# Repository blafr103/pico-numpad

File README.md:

# pico-numpad

Custom-built 17-key USB HID numpad powered by a Raspberry Pi Pico W,
featuring a hand-wired switch matrix, 16×2 LCD interface,
host-integrated PC monitoring, weather display, and onboard calculator.

The enclosure, electronics, and firmware were designed specifically for
this project using CircuitPython with event-driven matrix scanning via
`keypad.KeyMatrix`.

This README documents the hand-wired prototype. A custom two-layer PCB
successor built around a bare RP2040 is documented in
[`hardware/`](hardware/).

## Features

- USB HID numeric keypad
- Event-driven matrix scanning (`keypad.KeyMatrix`)
- 16x2 LCD with switchable views:
  - Clock + weather (current conditions and local time for one of
    four preset Canadian locations; date + time synced from the host)
  - PC stats, 4 cycling pages: overview (CPU/GPU utilization,
    temperature, package power), memory (RAM utilization, DIMM
    temperatures, VRAM), clocks (P/E-core max, GPU, TjMax
    distance), and voltages
  - Calculator (+ - * / with standard precedence; expression on
    row 0, result on Enter; keys are captured while active and
    send nothing to the PC)
  - Lifetime keypress statistics
- NumLock doubles as a momentary Fn key:
  - Fn+0: Clock view; pressed again while on it, cycles the
    weather location
  - Fn+1: PC stats view; pressed again while on it, cycles the
    stat pages
  - Fn+2: Calculator view; pressed again while on it, clears
  - Fn+3: Statistics view
  - Fn+'+': Increase keypad LED brightness
  - Fn+'-': Decrease keypad LED brightness
- Persistent settings (lifetime key counter and LED brightness) are stored in the
CircuitPython filesystem (`/count.txt` on internal flash).
- Automatic LCD backlight/LED timeout after 300 seconds of inactivity
- Optional Python companion application providing local time,
weather (Environment Canada API), and PC hardware monitoring.

<p align="center">
  <table align="center">
    <tr>
      <td align="center" width="450" valign="top">
        <br>
        <b>Finished Device</b>
      </td>
      <td align="center" width="470" valign="top">
        <br>
        <b>Hand-Wired Matrix</b>
      </td>
    </tr>
  </table>
</p>

## Physical Construction

This prototype is entirely hand-built rather than assembled on a PCB. The
hand-wired construction allowed the electrical design, firmware, and enclosure
to be developed and validated before committing to a dedicated PCB. That board
now exists as rev A and is documented in [`hardware/`](hardware/).

### Enclosure

- Designed from scratch in Autodesk Fusion 360
- 3D printed on a Bambu Lab X1 Carbon using PETG for the structural components and translucent polycarbonate (PC) for the light-diffusing enclosure 
- Two-piece printed enclosure with integrated LCD mount and switch plate
- Translucent white PC diffuses the per-key LEDs

### Switches & Keycaps

- Switches: Gateron KS-9 G Pro Black linear switches
- Keycaps: Ranked POM Jelly Premium Translucent keycaps

### Key Matrix

The keypad is wired as a 5×4 switch matrix with one diode per key to eliminate
ghosting.

Color coding throughout the wiring:

| Color | Function |
| :--- | :--- |
| **Red** | Matrix columns |
| **Yellow** | Matrix rows |
| **Orange** | LED power distribution |
| **Black** | LED ground |

Each switch includes a **1N4148** diode (anode toward the row, cathode toward
the column), matching the firmware configuration
(`columns_to_anodes=False`). The matrix layout and diode orientation were
verified using the included `tools/matrix_map_test.py` and
`tools/diode_test.py` utilities.

Note that the rev A PCB in [`hardware/`](hardware/) uses the opposite
orientation (cathode to row).

### Lighting

- One discrete white LED beneath each key
- LEDs share a common PWM-controlled supply, with each LED using its own **100 Ω** current-limiting resistor
- Brightness is adjustable in 12.5% increments using **Fn + '+'** and **Fn + '-'**
- The selected brightness is persisted across power cycles
- LEDs turn off together with the LCD backlight after the inactivity timeout and are restored automatically on activity

### Electronics

- Raspberry Pi Pico W mounted internally
- HD44780-compatible 16×2 LCD with PCF8574 I²C backpack

## Hardware

- Raspberry Pi Pico W (RP2040), CircuitPython 9.2.1
- 16×2 HD44780-compatible LCD with PCF8574 I²C backpack (0x27)
- 17 Gateron KS-9 G Pro Black switches
- Ranked POM Jelly translucent keycaps
- 17 white discrete LEDs
- Rows: GP2–GP6
- Columns: GP12–GP15
- Key LEDs (PWM): GP11
- I²C: SDA GP0 · SCL GP1

## Install

1. Flash CircuitPython 9.x to the Pico.
2. Copy `code.py`, `boot.py`, and `lib/` to the CIRCUITPY drive,
   then power cycle (`boot.py` changes only apply at power-up).
   - On first boot, the firmware creates `/count.txt` to store persistent settings (currently the lifetime keypress count and LED brightness).
3. Install `adafruit_hid` from the
   [CircuitPython 9.x library bundle](https://circuitpython.org/libraries)
   into `lib/`.
4. Optional, for the clock, weather, and PC stats:
   `pip install pyserial requests env_canada` on the PC and run
   `python host/companion.py`. The pad is fully functional without
   it; the clock shows UNKNOWN, weather shows "no weather", and PC
   stats show "no data" until first contact.
   - The Pico exposes two serial ports; the script auto-detects
     the data port, or set PORT in the script manually.
   - PC stats additionally require
     [LibreHardwareMonitor](https://github.com/LibreHardwareMonitor/LibreHardwareMonitor)
     running as administrator with its web server enabled
     (Options - Remote Web Server - Run). Time and weather work
     without it.
   - Weather locations are configured in companion.py as
     label + coordinates + IANA timezone.
   - For hands-off startup on Windows (Task Scheduler setup, logging,
    troubleshooting), see [host/README.md](host/README.md).

## Design

Matrix scanning and debouncing run in C in the background
(`keypad.KeyMatrix`, 10 ms interval); the main loop only consumes
queued edge events, so a busy loop delays input rather than dropping
it. HID output uses `press()`/`release()` on edges so the host sees
real held keys and handles auto-repeat. A hand-written equivalent of
the scanner (polling, per-key debounce state machine) is kept in
[`reference/`](reference/) with a comparison of the two approaches.

`columns_to_anodes=False` is required for this board's diode
orientation; the default silently reads all keys as dead.

`boot.py` remounts the filesystem to allow the firmware to save the
persistent key counter. Holding **NumLock** while connecting the Pico
starts a development mode that leaves the drive writable from the host
and disables persistence.

The LCD is driven with no `sleep()` in the main loop: dirty-flag
rendering (I²C writes only on state change), fixed-width line
overwrites instead of `clear()`, and edge-triggered backlight
control. A full LCD line write costs ~50 ms over I²C, so
unconditional redraws would starve input latency.

The LCD is organized as switchable views (splash on boot, clock,
PC stats, calculator, statistics). Holding **NumLock** acts as a
momentary Fn key: tapping a digit while held switches views without
typing it. A plain NumLock tap is deferred until release so tap and
hold can be distinguished without affecting normal typing. Each view
owns its input: most pass keys through to the PC as normal typing,
while the calculator captures digits and operators entirely
(including suppressing their release events), so nothing leaks to
the host while it is active.

The calculator stores the expression as typed (row 0, scrolling
left past 16 characters) and evaluates on Enter with standard
precedence: tokens are reduced in two passes, folding `*` and `/`
left-to-right first, then summing the remaining `+`/`-` terms.
Divide-by-zero shows Error, cleared by the next digit. After a
result, a digit starts a fresh expression and an operator continues
from the result. Results too wide for the row use scientific
notation. Leaving the view clears it.

Time, weather, and PC stats come from an optional host script
(`host/companion.py`, setup and operation in
[host/README.md](host/README.md)) over a second USB CDC serial port
enabled in `boot.py`. The protocol is newline-terminated ASCII `key:value` lines;
the Pico is a pure listener and the host broadcasts unsolicited (time
on connect and every 30 s, stats every 2 s, weather every 10 min).
The clock free-runs on the crystal between syncs and re-anchors on
every message, bounding drift to one broadcast interval. The RP2040
has no battery-backed RTC, so time is lost at power-off and shows
UNKNOWN until the first sync.

Weather comes from Environment Canada via the `env_canada` package
(nearest site to each configured coordinate). The clock view shows
one location's conditions on row 0 and its local date/time on row 1;
the host sends each location's UTC-offset delta computed fresh with
`zoneinfo`, so DST is handled entirely host-side. Weather older than
30 minutes displays as stale (`LABEL --`); PC stats older than 15
seconds display as "no data".

PC stat rows are composed entirely on the host: companion.py reads
LibreHardwareMonitor's JSON endpoint, selects sensors by hardware
prefix and display name (numeric sensor indices shift between LHM
versions), and sends each page row as a finished 16-character line.
The Pico renders these verbatim, apart from substituting `*` with
the LCD's degree symbol, so adding or reworking a stat page is a
host-only change. Missing sensors render as `--`; the sensor names
target this machine's hardware and need adjusting for others.

Persistent settings (currently the lifetime keypress count and LED brightness) 
are stored in `/count.txt`. To minimize flash wear, writes are batched 
(100 keypresses by default) and also occur immediately after brightness 
changes and when the device transitions to the idle state.

The firmware is organized into independent subsystems for input handling,
LCD rendering, view management, HID output, persistent settings, and host 
communication.

## Future Improvements

- User-configurable key mapping and macros
- More robust persistent configuration storage
  
The custom PCB, integrated USB-C, and per-key RGB lighting items previously
listed here are addressed by the rev A board in [`hardware/`](hardware/).

## Tools

- `tools/matrix_map_test.py` prints (row, col) per keypress; used
  to build/verify the keymap
- `tools/diode_test.py` is a bidirectional scan; verifies diode
  presence and orientation per key

Run either by copying to CIRCUITPY as `code.py` (back up first) and
watching the serial console. Run in dev mode (NumLock at plug-in)
so the drive is writable.

## Credits

LCD driver (`lib/lcd.py`, `lib/i2c_pcf8574_interface.py`):
[dwhall/circuitpython_lcd](https://github.com/dwhall/circuitpython_lcd),
original license headers retained.

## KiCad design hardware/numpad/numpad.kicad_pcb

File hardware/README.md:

# pico-numpad - Hardware

Custom two-layer PCB for a 17-key USB numpad with per-key RGB, a rotary encoder, and a 16x2 character LCD. This is the custom-board successor to the hand-wired CircuitPython numpad documented in the repository root, rebuilt around a bare RP2040 with hot-swap switches.
 
**Status - Rev A.** Design complete, DRC clean, full design review passed. Boards fabricated by PCBWay (ENIG) and hand-assembled. Electrical bring-up is **in progress and incomplete** - the board does not yet enumerate over USB and the 3.3 V rail is under investigation. The C firmware targeting this board has been started but is not yet functional. Treat the design as unvalidated.
 
Designed in KiCad 10.

---

## Features

- Bare **RP2040** (not a Pico module) with 16 MB **W25Q128** QSPI flash and a 12 MHz crystal
- **17 hot-swap keys** on Kailh MX sockets (CPG151101S11), any MX-style switch
- **Per-key RGB** - 17x SK6812MINI-E, 5 V data driven through a 74AHCT1G125 level buffer
- **Rotary encoder** with push (EC11), push mapped into the key matrix
- **16x2 HD44780 LCD** over I2C (PCF8574 backpack), driven through an onboard level shifter and connected via header
- **USB-C** with dual 5.1 kΩ CC pulldowns, USBLC6-2SC6 ESD protection, and 27 Ω series termination
- 5x4 diode-per-key matrix, one 1N4148 per switch, **cathode to row** (COL2ROW). This is the reverse of the hand-wired build, which is wired anode to row.
- BOOTSEL and RESET buttons, SWD header
- Screws enter from either face (bottom edge extended so the lower mounting holes clear the 0 and Enter keycaps)

---

## Repository layout

```
hardware/
├── README.md                            this file
├── numpad/
│   ├── numpad.kicad_pro                 KiCad project
│   ├── numpad.kicad_prl                 project-local settings (editor state, netclasses)
│   ├── numpad.kicad_pcb                 board
│   ├── numpad.kicad_sch                 schematic, root sheet
│   ├── 01_power_usb.kicad_sch           USB-C, ESD, 3.3 V regulator
│   ├── 02_mcu.kicad_sch                 RP2040, QSPI flash, crystal, SWD, BOOTSEL/RESET
│   ├── 03_matrix.kicad_sch              key matrix and rotary encoder
│   ├── 04_rgb.kicad_sch                 SK6812 chain and 74AHCT1G125 buffer
│   ├── 05_ui.kicad_sch                  LCD header and I2C level shifters
│   ├── fp-lib-table                     footprint library table
│   ├── sym-lib-table                    symbol library table
│   ├── numpad.csv                       BOM export from the schematic
│   ├── part-numbers.txt                 working notes on ordered part numbers
│   ├── lib/marbastlib/                  git submodule - MX symbols/footprints, Kailh sockets
│   ├── plot-files/                      raw KiCad plot output - all gerbers, both drill maps, DXF, drills
│   ├── numpad-revA-fab/                 cleaned fab set actually sent to the fab (12 files)
│   ├── numpad-revA-fab.zip              the same set, zipped for upload
│   ├── step-files/                      board STEP for the enclosure model
│   └── W1129510AS1K1.pdf                PCBWay order document, W1129510AS1K1
├── stencil_gerbers/                     paste and outline set sent for the SMD stencils
├── stencil_gerbers.zip                  the same set, zipped for upload
├── production file W1129510AS1K2/       PCBWay's returned CAM data for W1129510AS1K2
└── production file W1129510AS1K2.zip    the same, as delivered
```

`numpad/lib/marbastlib` is a submodule. After cloning:

```
git submodule update --init --recursive
```

---

## Board summary

| | |
|---|---|
| Size | 83 x 127 mm |
| Layers | 2 |
| Thickness | 1.6 mm |
| Copper | 1 oz |
| Min track / clearance | 0.2 mm / 0.15 mm |
| Vias | 0.6 / 0.3 mm |
| Footprints | 120 |

Switches and RGB are surface-mount on the **back** copper (marbastlib MX footprints are authored for back-side placement). The USB/MCU/encoder strip sits along the top edge on the front.

---

## Key matrix

17 keys plus the encoder push occupy 18 of the 20 cells in a 5x4 grid. The 2u-tall `+` and `Enter` keys each take a single electrical cell, at R1C3 and R4C3, which leaves R2C3 free for the encoder push and R3C3 unused. The 2u-wide `0` key leaves R4C1 unused.

| | C0 | C1 | C2 | C3 |
|----|-----|---------|-----|--------------|
| R0 | Num | /       | *   | -            |
| R1 | 7   | 8       | 9   | +            |
| R2 | 4   | 5       | 6   | Encoder push |
| R3 | 1   | 2       | 3   | (unused)     |
| R4 | 0   | (unused) | .  | Enter        |

---

## Notable ICs and interfaces

| Ref | Part | Role |
|-----|------|------|
| U3  | RP2040 | MCU, QFN-56, 0.4 mm pitch |
| U4  | W25Q128JVS | 16 MB QSPI program flash |
| U1  | NCP1117-3.3 | 3.3 V LDO (see substitution note below) |
| U2  | USBLC6-2SC6 | USB ESD protection |
| U5  | 74AHCT1G125 | 3.3 V to 5 V buffer for the RGB data line |
| Q1/Q2 | BSS138 x2 | I2C level shift for the LCD header |
| J1  | USB-C receptacle (HRO TYPE-C-31-M-12) | Power and data |
| J2  | SWD header | Debug |
| J3  | LCD header | I2C to the character LCD |

Exact GPIO assignments live in the schematic and are the source of truth for firmware. Verified against the KiCad netlist: RGB data on **GP11**, encoder A/B on **GP7/GP8**. The matrix rows (GP2-GP6), columns (GP12-GP15), and I2C (GP0/GP1) carry over unchanged from the hand-wired build. GP11 changes role, it drove the single-colour LED PWM on the hand-wired unit and drives the SK6812 chain here. The encoder is new to this board.

---

## Ordering this board

Fab specs, all inside a standard 2-layer capability:
 
- 2-layer, 1.6 mm FR-4, 1 oz copper
- 6/6 mil track/space class, 0.3 mm minimum drill
- **ENIG recommended.** The RP2040 is a 0.4 mm-pitch QFN-56 - a flat immersion-gold finish wets far more predictably under hand soldering than domed HASL
- 
The board has **6 intentional plated slots** (4 at the USB-C connector shield legs, 2 at the encoder bracket), written as route-mode Excellon (`G00/M15/M16`) rather than G85. Most CAM tools read this correctly, but it is worth confirming in the fab's gerber viewer that they render as elongated openings.

---

## Assembly and bring-up

The board is designed for **staged bring-up**, not a single reflow:
 
1. Populate the USB-C and regulator section first. Scope the 3.3 V rail under a ~100 Ω load (AC-coupled, bandwidth-limited, short ground spring) and confirm it is not oscillating **before** placing the RP2040.
2. Then place the MCU, flash, and crystal, and confirm enumeration over USB.
3. Then the switch matrix, encoder, RGB chain, and LCD header.

Two part choices worth considering before assembly:
 
- **Regulator.** The board is drawn for the NCP1117ST33T3G, but C2 is a 10 µF MLCC that sits below that regulator's 0.25-2.2 Ω output-ESR floor. If the 3.3 V rail oscillates, swap in a ceramic-stable **TLV1117-33** (same SOT-223 pinout, drop-in). Recommend ordering both for cheap insurance.
- **Crystal.** 12 MHz 3225, chosen for **CL ≈ 18 pF** to match the 27 pF loading caps. Check the specific part's max ESR - higher-CL parts trend higher ESR, and higher CL also slows startup, which may need the pico-sdk XOSC startup multiplier raised. A CL = 10 pF part with 15 pF caps is a BOM-only fallback if either becomes a problem.

---

## Firmware

The hand-wired numpad in the repository root runs **CircuitPython** on a Pico W. That firmware does **not** port directly to this board - the bare RP2040 boot flow, the encoder, and RGB (vs single-color PWM) all differ, as does the diode orientation. The matrix and I2C pin assignments do carry over.
 
The custom board is designed to run a **C firmware on pico-sdk + TinyUSB**. That rewrite has been started and is not yet functional.

---

## License

The files in this repository are covered by the license terms in the repository root.
 
The KiCad symbols and footprints under `numpad/lib/marbastlib` are a git submodule of [ebastler/marbastlib](https://github.com/ebastler/marbastlib), licensed **CERN-OHL-P-2.0**. Those terms, including its notice requirements, apply to that library and to the footprints used from it.

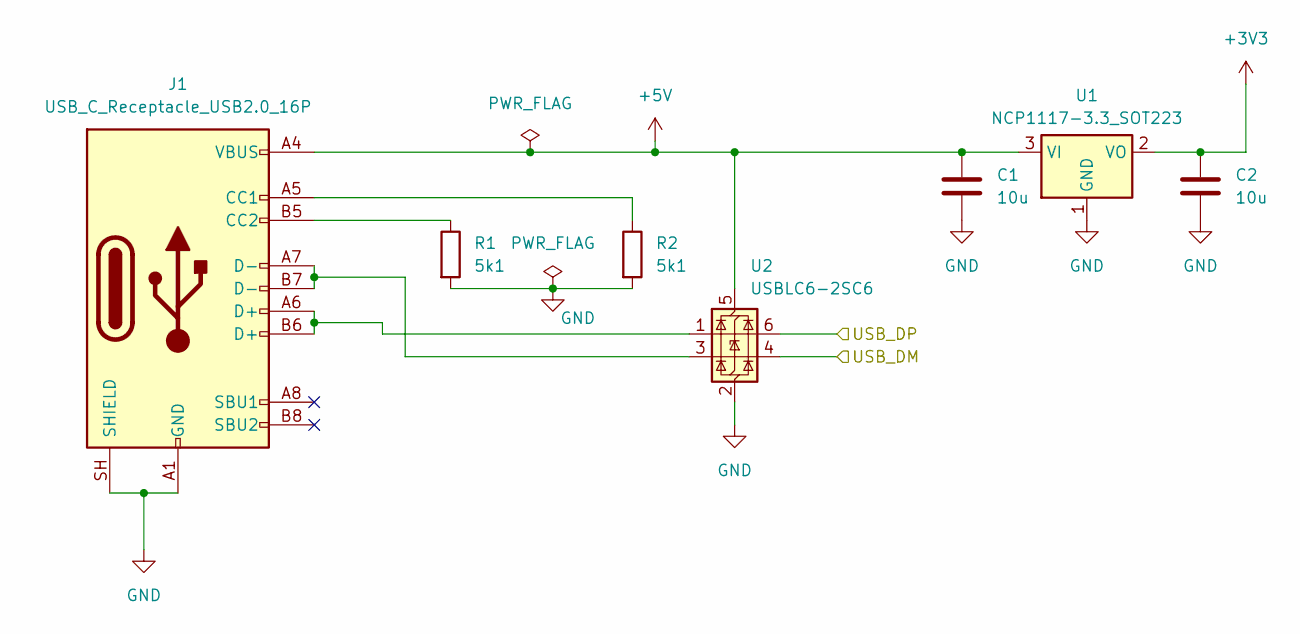
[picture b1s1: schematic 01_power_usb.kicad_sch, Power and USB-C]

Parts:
C1, C2: 10u; C_0805_2012Metric
J1: USB_C_Receptacle_USB2.0_16P; USB_C_Receptacle_HRO_TYPE-C-31-M-12
R1, R2: 5k1; R_0603_1608Metric
U1: NCP1117-3.3_SOT223; SOT-223-3_TabPin2
U2: USBLC6-2SC6; SOT-23-6

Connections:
+3V3: C2.1, U1.2 (VO); also elsewhere on the board
+5V: C1.1, J1.A4 (VBUS), J1.A9 (VBUS), J1.B4 (VBUS), J1.B9 (VBUS), U1.3 (VI), U2.5 (VBUS); also elsewhere on the board
/01_power_usb/USB_DM: U2.4 (I/O2); also elsewhere on the board
/01_power_usb/USB_DP: U2.6 (I/O1); also elsewhere on the board
GND: C1.2, C2.2, J1.A1 (GND), J1.A12 (GND), J1.B1 (GND), J1.B12 (GND), J1.SH (SHIELD), R1.2, R2.2, U1.1 (GND), U2.2 (GND); also elsewhere on the board
unnamed: J1.A5 (CC1), R2.1
unnamed: J1.B5 (CC2), R1.1
unnamed: J1.A6 (D+), J1.B6 (D+), U2.1 (I/O1)
unnamed: J1.A7 (D-), J1.B7 (D-), U2.3 (I/O2)

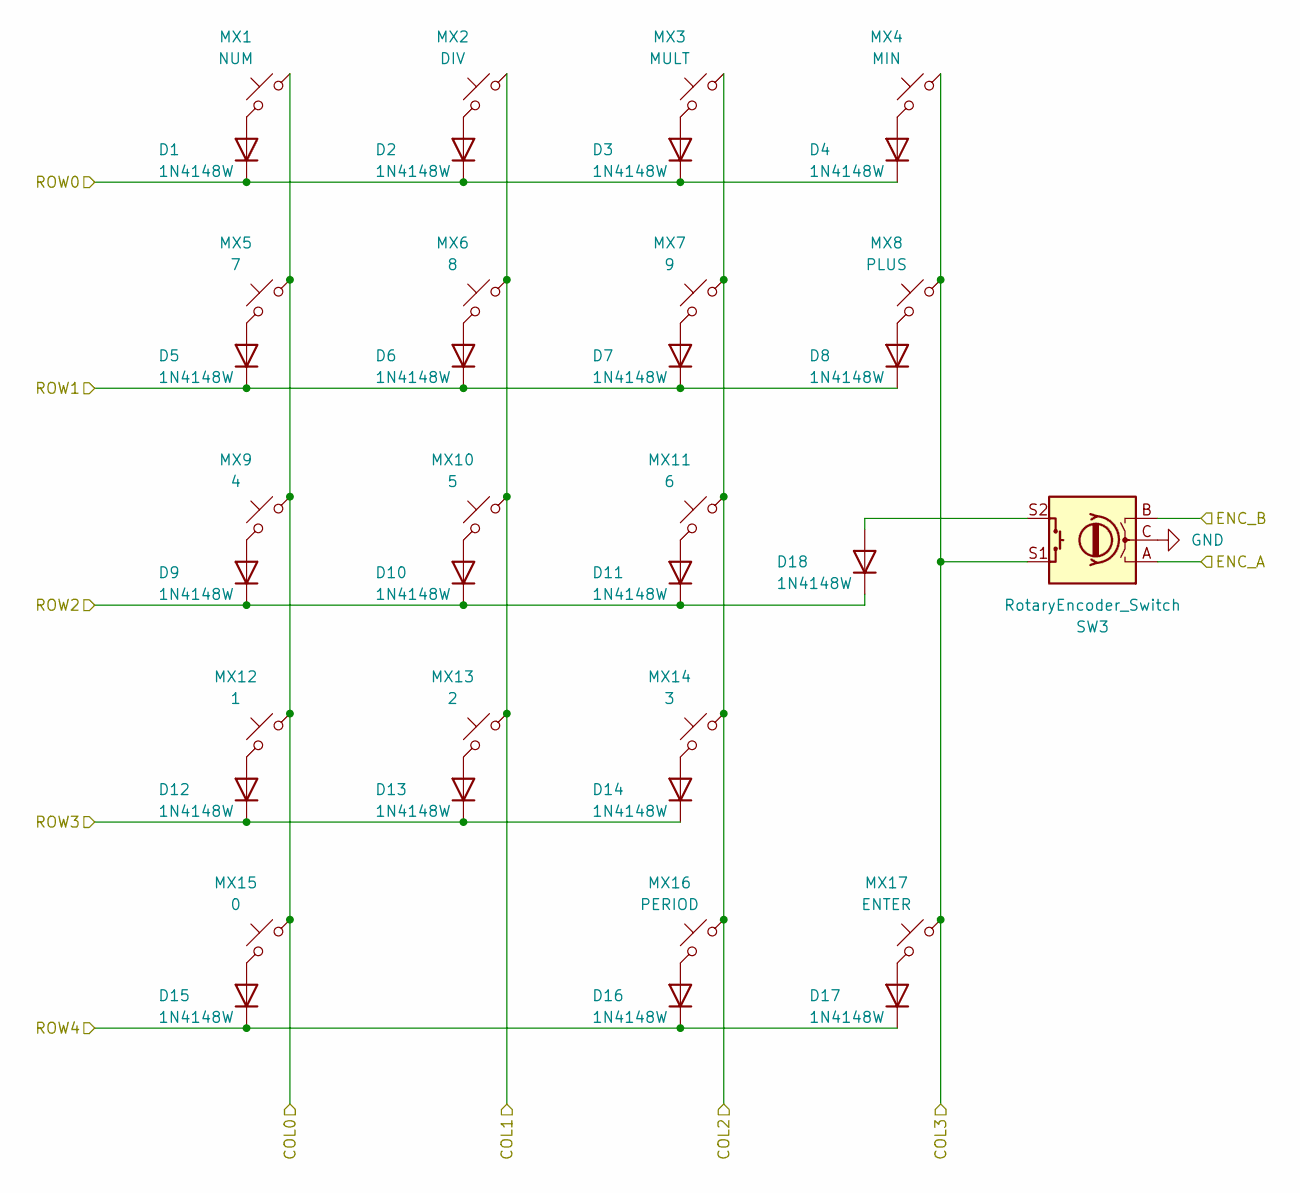
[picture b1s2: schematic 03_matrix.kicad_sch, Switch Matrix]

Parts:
D1, D2, D3, D4, D5, D6, D7, D8, D9, D10, D11, D12, D13, D14, D15, D16, D17, D18: 1N4148W; D_SOD-123
MX1: NUM; SW_MX_HS_CPG151101S11_1u
MX2: DIV; SW_MX_HS_CPG151101S11_1u
MX3: MULT; SW_MX_HS_CPG151101S11_1u
MX4: MIN; SW_MX_HS_CPG151101S11_1u
MX5: 7; SW_MX_HS_CPG151101S11_1u
MX6: 8; SW_MX_HS_CPG151101S11_1u
MX7: 9; SW_MX_HS_CPG151101S11_1u
MX8: PLUS; SW_MX_HS_CPG151101S11_1u
MX9: 4; SW_MX_HS_CPG151101S11_1u
MX10: 5; SW_MX_HS_CPG151101S11_1u
MX11: 6; SW_MX_HS_CPG151101S11_1u
MX12: 1; SW_MX_HS_CPG151101S11_1u
MX13: 2; SW_MX_HS_CPG151101S11_1u
MX14: 3; SW_MX_HS_CPG151101S11_1u
MX15: 0; SW_MX_HS_CPG151101S11_1u
MX16: PERIOD; SW_MX_HS_CPG151101S11_1u
MX17: ENTER; SW_MX_HS_CPG151101S11_1u
SW3: RotaryEncoder_Switch; RotaryEncoder_Alps_EC11E-Switch_Vertical_H20mm

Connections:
/02_mcu/COL0: MX1.2, MX5.2, MX9.2, MX12.2, MX15.2; also elsewhere on the board
/02_mcu/COL1: MX2.2, MX6.2, MX10.2, MX13.2; also elsewhere on the board
/02_mcu/COL2: MX3.2, MX7.2, MX11.2, MX14.2, MX16.2; also elsewhere on the board
/02_mcu/COL3: MX4.2, MX8.2, MX17.2, SW3.S1; also elsewhere on the board
/02_mcu/ENC_A: SW3.A; also elsewhere on the board
/02_mcu/ENC_B: SW3.B; also elsewhere on the board
/02_mcu/ROW0: D1.1 (K), D2.1 (K), D3.1 (K), D4.1 (K); also elsewhere on the board
/02_mcu/ROW1: D5.1 (K), D6.1 (K), D7.1 (K), D8.1 (K); also elsewhere on the board
/02_mcu/ROW2: D9.1 (K), D10.1 (K), D11.1 (K), D18.1 (K); also elsewhere on the board
/02_mcu/ROW3: D12.1 (K), D13.1 (K), D14.1 (K); also elsewhere on the board
/02_mcu/ROW4: D15.1 (K), D16.1 (K), D17.1 (K); also elsewhere on the board
GND: SW3.C; also elsewhere on the board
unnamed: D1.2 (A), MX1.1
unnamed: D2.2 (A), MX2.1
unnamed: D3.2 (A), MX3.1
unnamed: D4.2 (A), MX4.1
unnamed: D5.2 (A), MX5.1
unnamed: D6.2 (A), MX6.1
unnamed: D7.2 (A), MX7.1
unnamed: D8.2 (A), MX8.1
unnamed: D9.2 (A), MX9.1
unnamed: D10.2 (A), MX10.1
unnamed: D11.2 (A), MX11.1
unnamed: D12.2 (A), MX12.1
unnamed: D13.2 (A), MX13.1
unnamed: D14.2 (A), MX14.1
unnamed: D15.2 (A), MX15.1
unnamed: D16.2 (A), MX16.1
unnamed: D17.2 (A), MX17.1
unnamed: D18.2 (A), SW3.S2

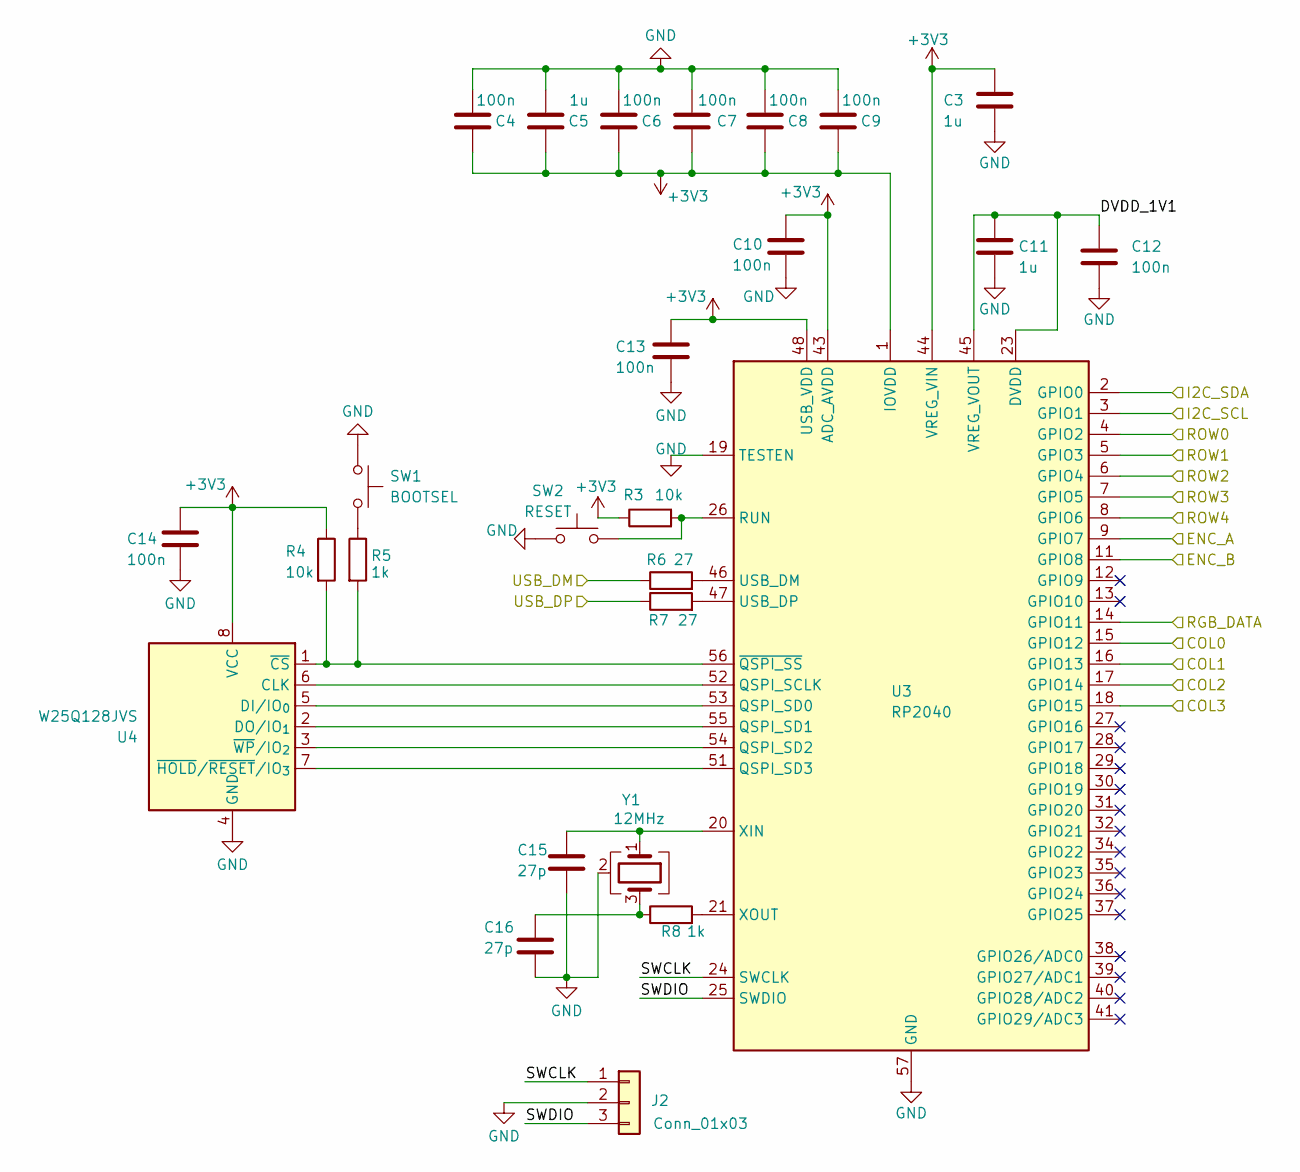
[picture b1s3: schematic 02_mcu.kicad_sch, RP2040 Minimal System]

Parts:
C3, C5, C11: 1u; C_0603_1608Metric
C4, C6, C7, C8, C9, C10, C12, C13, C14: 100n; C_0603_1608Metric
C15, C16: 27p; C_0603_1608Metric
J2: Conn_01x03; PinHeader_1x03_P2.54mm_Vertical
R3, R4: 10k; R_0603_1608Metric
R5, R8: 1k; R_0603_1608Metric
R6, R7: 27; R_0603_1608Metric
SW1: BOOTSEL; SW_SPST_PTS645Sx43SMTR92
SW2: RESET; SW_SPST_PTS645Sx43SMTR92
U3: RP2040; QFN-56-1EP_7x7mm_P0.4mm_EP3.2x3.2mm
U4: W25Q128JVS; SOIC-8_5.3x5.3mm_P1.27mm
Y1: 12MHz; Crystal_SMD_3225-4Pin_3.2x2.5mm

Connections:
+3V3: C3.1, C4.1, C5.1, C6.1, C7.1, C8.1, C9.1, C10.1, C13.1, C14.1, R3.1, R4.1, U3.1 (IOVDD), U3.10 (IOVDD), U3.22 (IOVDD), U3.33 (IOVDD), U3.42 (IOVDD), U3.43 (ADC_AVDD), U3.44 (VREG_VIN), U3.48 (USB_VDD), U3.49 (IOVDD), U4.8 (VCC); also elsewhere on the board
/01_power_usb/USB_DM: R6.1; also elsewhere on the board
/01_power_usb/USB_DP: R7.1; also elsewhere on the board
/02_mcu/COL0: U3.15 (GPIO12); also elsewhere on the board
/02_mcu/COL1: U3.16 (GPIO13); also elsewhere on the board
/02_mcu/COL2: U3.17 (GPIO14); also elsewhere on the board
/02_mcu/COL3: U3.18 (GPIO15); also elsewhere on the board
/02_mcu/DVDD_1V1: C11.1, C12.1, U3.23 (DVDD), U3.45 (VREG_VOUT), U3.50 (DVDD)
/02_mcu/ENC_A: U3.9 (GPIO7); also elsewhere on the board
/02_mcu/ENC_B: U3.11 (GPIO8); also elsewhere on the board
/02_mcu/I2C_SCL: U3.3 (GPIO1); also elsewhere on the board
/02_mcu/I2C_SDA: U3.2 (GPIO0); also elsewhere on the board
/02_mcu/RGB_DATA: U3.14 (GPIO11); also elsewhere on the board
/02_mcu/ROW0: U3.4 (GPIO2); also elsewhere on the board
/02_mcu/ROW1: U3.5 (GPIO3); also elsewhere on the board
/02_mcu/ROW2: U3.6 (GPIO4); also elsewhere on the board
/02_mcu/ROW3: U3.7 (GPIO5); also elsewhere on the board
/02_mcu/ROW4: U3.8 (GPIO6); also elsewhere on the board
/02_mcu/SWCLK: J2.1, U3.24 (SWCLK)
/02_mcu/SWDIO: J2.3, U3.25 (SWDIO)
GND: C3.2, C4.2, C5.2, C6.2, C7.2, C8.2, C9.2, C10.2, C11.2, C12.2, C13.2, C14.2, C15.2, C16.2, J2.2, SW1.1, SW2.1, U3.19 (TESTEN), U3.57 (GND), U4.4 (GND), Y1.2 (G), Y1.4 (G); also elsewhere on the board
unnamed: C16.1, R8.1, Y1.3
unnamed: R5.1, SW1.2
unnamed: U3.52 (QSPI_SCLK), U4.6 (CLK)
unnamed: U3.53 (QSPI_SD0), U4.5 (DI/IO_{0})
unnamed: U3.55 (QSPI_SD1), U4.2 (DO/IO_{1})
unnamed: U3.54 (QSPI_SD2), U4.3 (~WP/IO_{2})
unnamed: U3.51 (QSPI_SD3), U4.7 (~HOLD/~RESET/IO_{3})
unnamed: R3.2, SW2.2, U3.26 (RUN)
unnamed: R6.2, U3.46 (USB_DM)
unnamed: R7.2, U3.47 (USB_DP)
unnamed: C15.1, U3.20 (XIN), Y1.1
unnamed: R8.2, U3.21 (XOUT)
unnamed: R4.2, R5.2, U3.56 (~QSPI_SS), U4.1 (~CS)

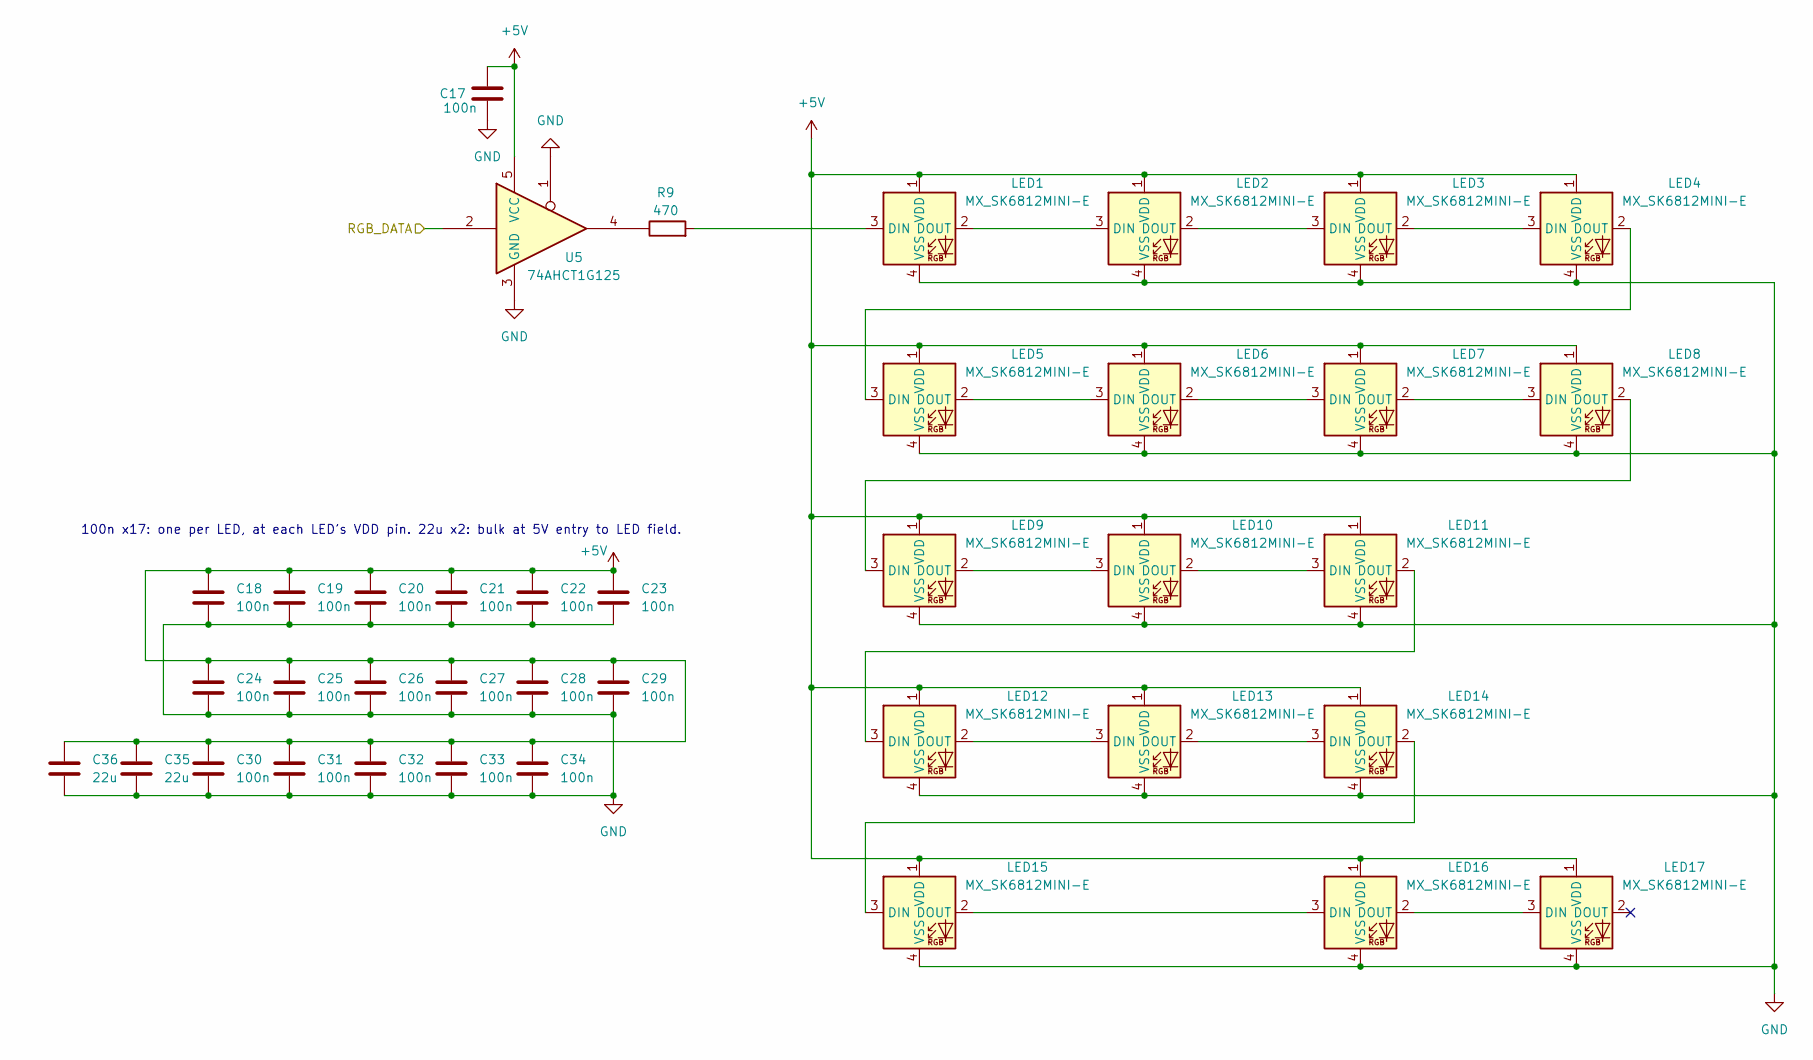
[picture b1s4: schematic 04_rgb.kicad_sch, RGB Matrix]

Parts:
C17, C18, C19, C20, C21, C22, C23, C24, C25, C26, C27, C28, C29, C30, C31, C32, C33, C34: 100n; C_0603_1608Metric
C35, C36: 22u; C_0805_2012Metric
LED1, LED2, LED3, LED4, LED5, LED6, LED7, LED8, LED9, LED10, LED11, LED12, LED13, LED14, LED15, LED16, LED17: MX_SK6812MINI-E; LED_MX_6028R
R9: 470; R_0603_1608Metric
U5: 74AHCT1G125; SOT-23-5

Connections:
+5V: C17.1, C18.1, C19.1, C20.1, C21.1, C22.1, C23.1, C24.1, C25.1, C26.1, C27.1, C28.1, C29.1, C30.1, C31.1, C32.1, C33.1, C34.1, C35.1, C36.1, LED1.1 (VDD), LED2.1 (VDD), LED3.1 (VDD), LED4.1 (VDD), LED5.1 (VDD), LED6.1 (VDD), LED7.1 (VDD), LED8.1 (VDD), LED9.1 (VDD), LED10.1 (VDD), LED11.1 (VDD), LED12.1 (VDD), LED13.1 (VDD), LED14.1 (VDD), LED15.1 (VDD), LED16.1 (VDD), LED17.1 (VDD), U5.5 (VCC); also elsewhere on the board
/02_mcu/RGB_DATA: U5.2; also elsewhere on the board
GND: C17.2, C18.2, C19.2, C20.2, C21.2, C22.2, C23.2, C24.2, C25.2, C26.2, C27.2, C28.2, C29.2, C30.2, C31.2, C32.2, C33.2, C34.2, C35.2, C36.2, LED1.4 (VSS), LED2.4 (VSS), LED3.4 (VSS), LED4.4 (VSS), LED5.4 (VSS), LED6.4 (VSS), LED7.4 (VSS), LED8.4 (VSS), LED9.4 (VSS), LED10.4 (VSS), LED11.4 (VSS), LED12.4 (VSS), LED13.4 (VSS), LED14.4 (VSS), LED15.4 (VSS), LED16.4 (VSS), LED17.4 (VSS), U5.1, U5.3 (GND); also elsewhere on the board
unnamed: LED1.3 (DIN), R9.2
unnamed: LED1.2 (DOUT), LED2.3 (DIN)
unnamed: LED2.2 (DOUT), LED3.3 (DIN)
unnamed: LED3.2 (DOUT), LED4.3 (DIN)
unnamed: LED4.2 (DOUT), LED5.3 (DIN)
unnamed: LED5.2 (DOUT), LED6.3 (DIN)
unnamed: LED6.2 (DOUT), LED7.3 (DIN)
unnamed: LED7.2 (DOUT), LED8.3 (DIN)
unnamed: LED8.2 (DOUT), LED9.3 (DIN)
unnamed: LED9.2 (DOUT), LED10.3 (DIN)
unnamed: LED10.2 (DOUT), LED11.3 (DIN)
unnamed: LED11.2 (DOUT), LED12.3 (DIN)
unnamed: LED12.2 (DOUT), LED13.3 (DIN)
unnamed: LED13.2 (DOUT), LED14.3 (DIN)
unnamed: LED14.2 (DOUT), LED15.3 (DIN)
unnamed: LED15.2 (DOUT), LED16.3 (DIN)
unnamed: LED16.2 (DOUT), LED17.3 (DIN)
unnamed: R9.1, U5.4

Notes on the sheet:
100n x17: one per LED, at each LED's VDD pin. 22u x2: bulk at 5V entry to LED field.

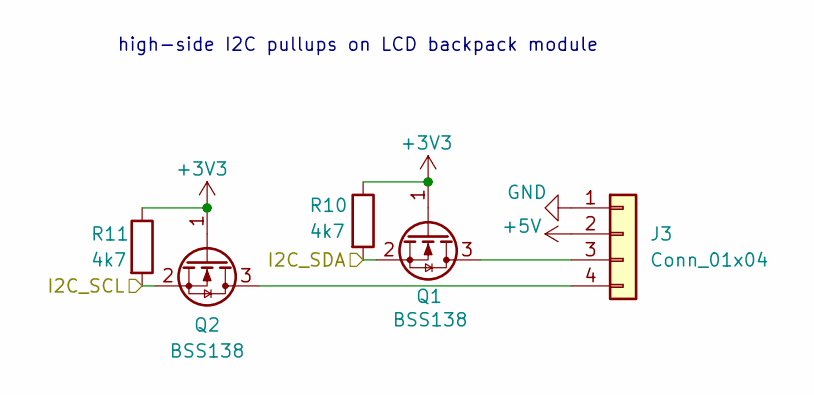
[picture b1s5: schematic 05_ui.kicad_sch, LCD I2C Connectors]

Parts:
J3: Conn_01x04; PinHeader_1x04_P2.54mm_Vertical
Q1, Q2: BSS138; SOT-23
R10, R11: 4k7; R_0603_1608Metric

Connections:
+3V3: Q1.1 (G), Q2.1 (G), R10.1, R11.1; also elsewhere on the board
+5V: J3.2; also elsewhere on the board
/02_mcu/I2C_SCL: Q2.2 (S), R11.2; also elsewhere on the board
/02_mcu/I2C_SDA: Q1.2 (S), R10.2; also elsewhere on the board
GND: J3.1; also elsewhere on the board
unnamed: J3.3, Q1.3 (D)
unnamed: J3.4, Q2.3 (D)

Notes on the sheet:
high-side I2C pullups on LCD backpack module

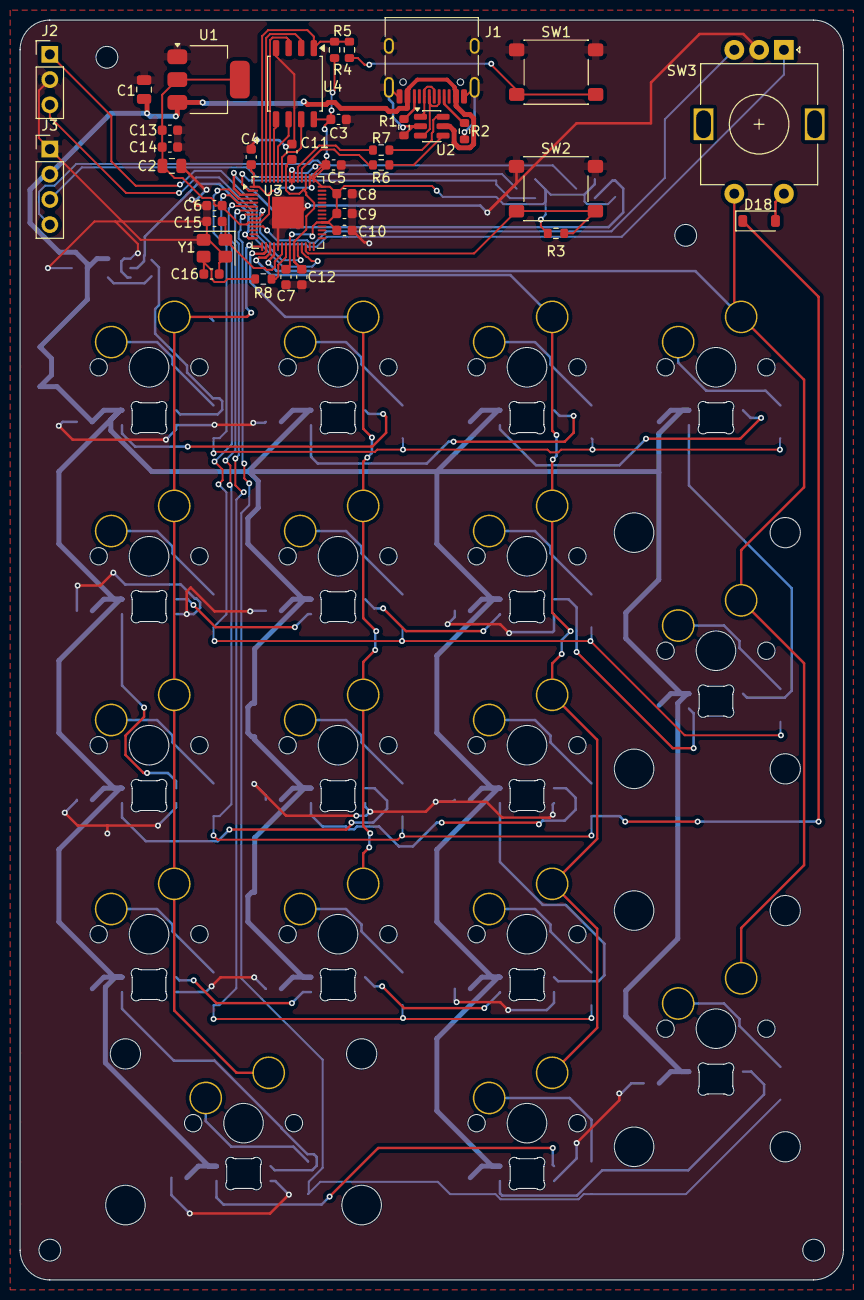
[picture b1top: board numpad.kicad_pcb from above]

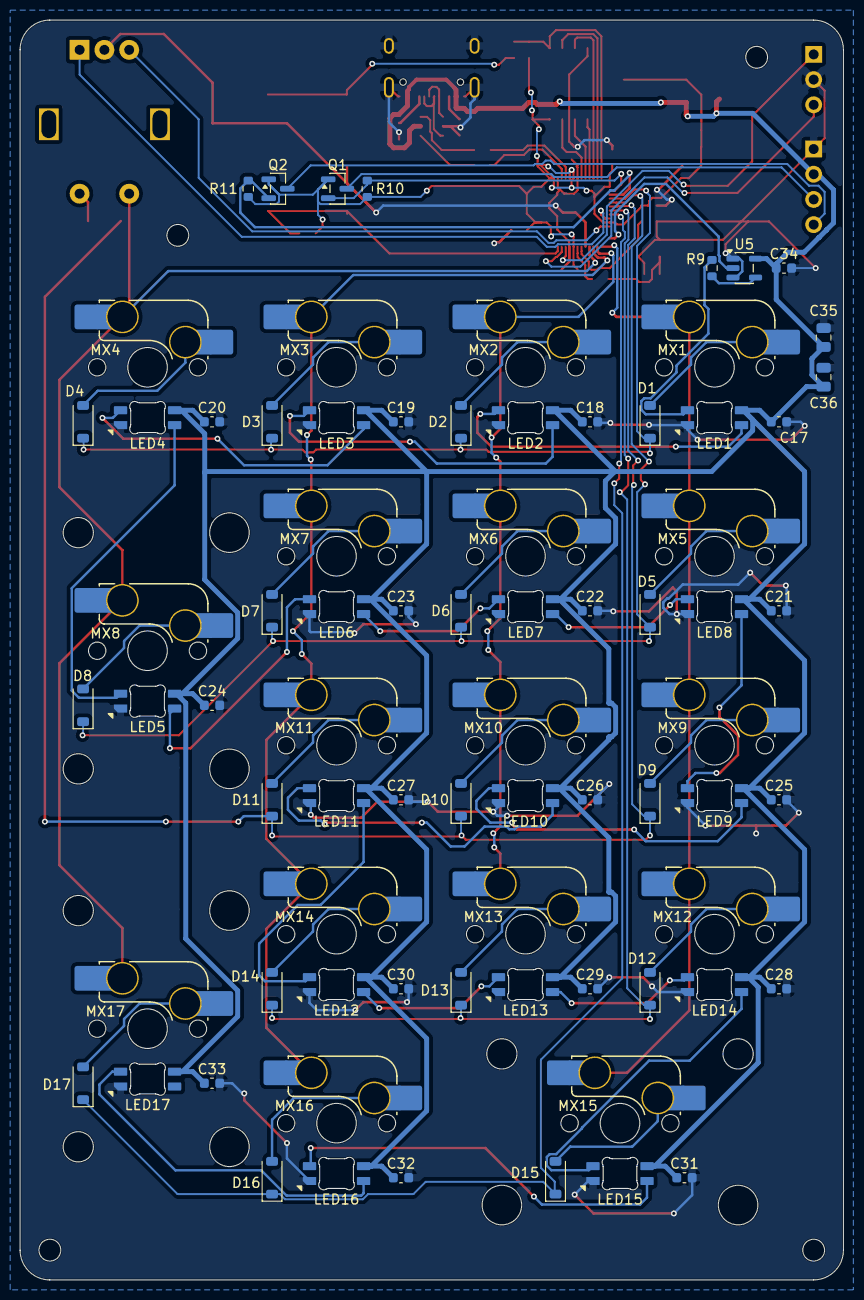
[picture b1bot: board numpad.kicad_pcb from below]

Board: 2 copper layers, 83.0 x 127.0 mm, 113 parts (77 on the bottom side), 77 nets.
